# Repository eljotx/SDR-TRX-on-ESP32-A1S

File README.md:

# SDR-TRX-on-ESP32-A1S -> JACK
This repository describes an SDR transceiver based on the ESP32 A1S processor, using an ILI9341 color touchscreen display, and a Si5351 oscillator. The program was written on the Arduino platform and is still in development, but the most important features have already been implemented and tested.
The most important part of the software is Arduino Audio Tools, authored by Phil Schatzmann: https://github.com/pschatzmann/arduino-audio-tools

# General Idea

The transceiver was built using a phase-based SSB signal generation method. Due to the breadth of the topic and the abundance of descriptions available online, this method will not be described here. However, I encourage you to study this topic theoretically, which will help you understand the presented solution.

Crucial to the solution is the use of **Tayloe mixer on FST3253, A/D conversion, Hilbert transforms, digital filters, and D/A conversion** in the audio paths of the receiver and transmitter.

## Local oscilator 

The Si5351 acts as a local oscillator, clocking the transmitter and receiver mixers at a frequency that ensures proper detection or modulation. In this case, the clock signals have a frequency twice that of the useful signal, with an additional 90-degree shift between them, achieved using an additional shaping circuit based on integrated circuits 7474 and 7486. It is possible to generate the mixer signals directly within the Si5351, but for operation above 3.5 MHz, the controller needs to be modified, but the biggest inconvenience is the need to reset the PLL synchronization loop. This synchronization generates delays that are perceived as strong clicks during receive mode.

## Tayloe Mixer

The FST3253 is a dual, quadruple, high-speed digital keyer that acts as a keyed mixer for both the transmitter and receiver. During reception, the mixer extracts the I and Q components from the received signal for further digital processing. During transmission, it modulates the RF signal with I and Q components, creating a lower or upper sideband signal.

## Processor ESP32 A1S

The core of the system is the ESP32 A1S processor, which is suitable for implementing the project because it contains built-in internal A/D and D/A converters and operates at a speed that allows for sufficiently fast sampling and the use of digital filters of desired complexity. Although the A/D and D/A converters have a resolution of 16 bits, this seems sufficient for a design that doesn't aspire to perfection, but rather addresses basic digital processing issues. Additionally, the processor has two cores, allowing for the separation of tasks that don't require immediate processing from those related to audio streaming. An additional advantage of the processor is the ability to use two I2c channels for communication with peripherals and a channel SPI for communication with the display. All of these features are discussed in more detail in the following descriptions.

# How receiver works
The antenna signal reaches a Tayloe mixer, where I and Q signals are generated. Both signals contain sideband information, which is used for digital data processing. To achieve this, the analog I and Q signals are digitized using 16-bit A/D converters. A Hilbert transform is then applied to one of the channels (shifting the signal's phase by 90 degrees). The signals are then digitally filtered using a BiQuad digital filter. Three filters are available: two low-pass filters at 3.6 kHz and 2.4 kHz, and a bandpass filter at 800 Hz for CW reception. Finally, the I and Q signals are converted back to analog using 16-bit D/A converters and summed, reducing the sideband of the received signal. The received sideband is selected in the Tayloe mixer by changing the phase of the heterodyne signals, reducing the load on the digital software.

The figure shows the signal waveform during reception in more detail. The antenna signal passes through an adjustable PIN diode attenuator and an ERA6 amplifier, and is then detected in the Taylor mixer. The I and Q signals extracted from the mixer, after summing, detection, and amplification, are used to adjust the gain using the PIN attenuator, and also, through AGC signal measurement, visualize the received signal strength. Simultaneously, the extracted I and Q signals undergo digital processing, as described earlier, and after conversion to analog and amplification, they can be received via headphones or a loudspeaker.

# How transceiver works

## SSB mode
In SSB mode, the transmitter initially digitizes the microphone signal using A/D converters. Subsequently, a Hilbert transform is performed on one of the signals, followed by a common LPF digital filtering with a 2.4 kHz bandwidth. This creates two digital I and Q signals, which are then converted to analog using D/A converters. The SSB signal is formed in a Tayloe mixer using two heterodyne signals that are 90 degrees out of phase. Similar to receiving, the sideband is selected by determining which heterodyne signal has a +90 degree offset relative to the other. This signal is then amplified and fed to the antenna. 

## CW mode
In CW mode, the Tayloe mixer is disabled (heterodyne stop), and an additional keyed heterodyne is activated at the device's operating frequency, with a sideband offset of approximately +800 Hz, depending on the sideband used.

In addition to the previously described CW and SSB signal generation process, the figure shows how common circuit elements are used. Specifically, the microphone signal is pre-amplified in the same amplifier used for reception, and after shaping the I and Q channels, it feeds the Tayloe mixer. The final output signal is generated at the Tayloe mixer output in SSB mode or directly from the Si5351 generator in CW mode.

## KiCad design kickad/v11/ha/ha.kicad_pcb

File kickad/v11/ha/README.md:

The system can be operated in a basic configuration without the AGC system and redundant components. The drawing shows which components do not need to be installed in such a case.
The red markings refer to the PIN diode attenuator. The purple markings refer to the input amplifier, which results in reduced receiver sensitivity. In both cases, the jumpers marked in blue must be installed.

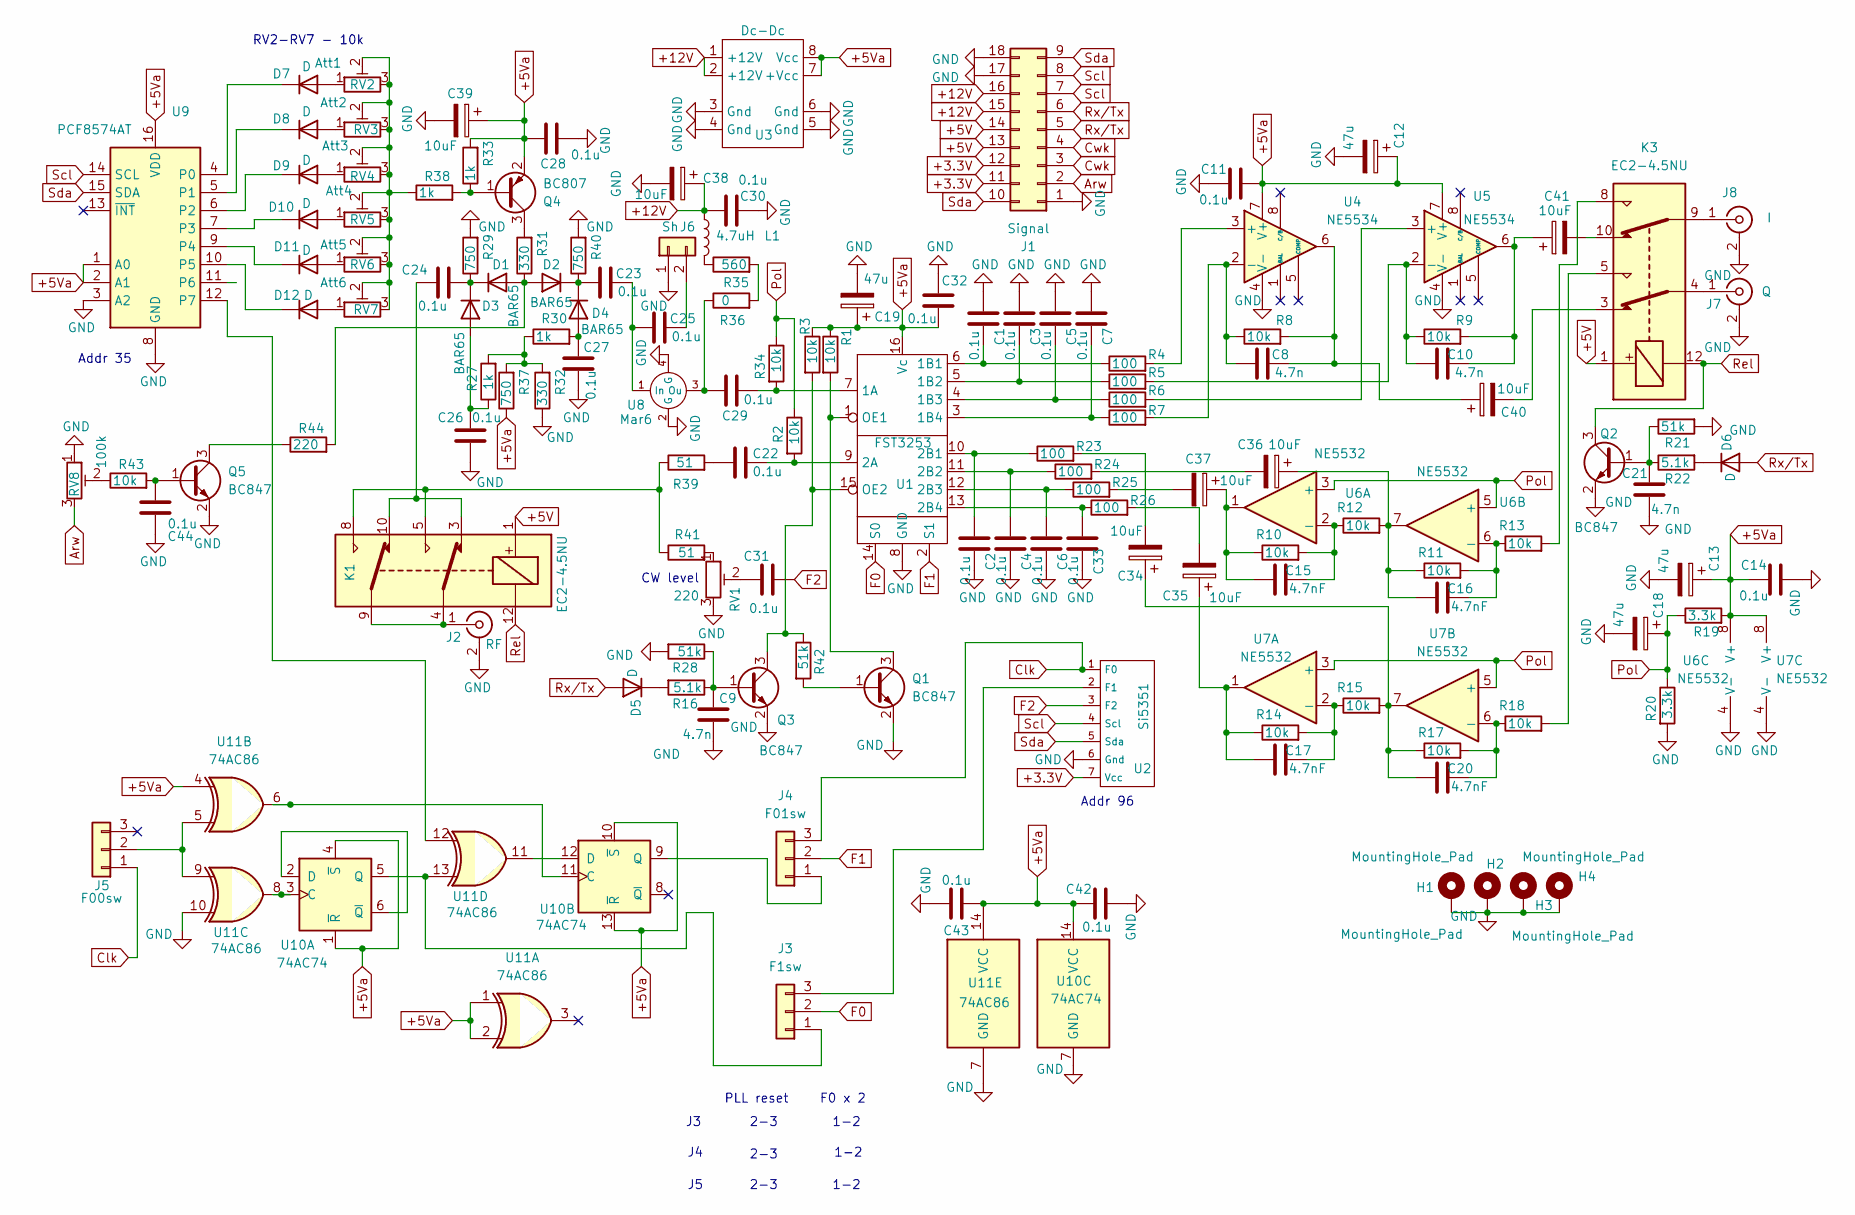
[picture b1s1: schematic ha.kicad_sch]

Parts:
C1, C2, C3, C4, C5, C6, C7, C11, C14, C22, C23, C24, C25, C26, C27, C28, C29, C30, C31, C32, C33, C42, C43, C44: 0.1u; C_0805_2012Metric
C8, C9, C10, C21: 4.7n; C_0805_2012Metric
C12, C13, C18, C19: 47u; CP_EIA-7343-31_Kemet-D
C15, C16, C17, C20: 4.7nF; C_0805_2012Metric
C34, C35, C36, C37, C38, C39, C40, C41: 10uF; C_1206_3216Metric
D1, D2, D3, D4: BAR65; C_0805_2012Metric
D5, D6, D7, D8, D9, D10, D11, D12: D; C_1206_3216Metric
H1, H2, H3, H4: MountingHole_Pad; MountingHole_3.2mm_M3_Pad_Via
J1: Signal; PinHeader_2x09_P2.54mm_Vertical
J2: RF; SMA_Amphenol_901-144_Vertical
J3: F1sw; PinHeader_1x03_P2.54mm_Vertical
J4: F01sw; PinHeader_1x03_P2.54mm_Vertical
J5: F00sw; PinHeader_1x03_P2.54mm_Vertical
J6: Sh; PinHeader_1x02_P2.54mm_Vertical
J7: Q; SMA_Amphenol_901-144_Vertical
J8: I; SMA_Amphenol_901-144_Vertical
K1, K3: EC2-4.5NU; Relay_DPDT_Kemet_EC2_NJ
L1: 4.7uH; L_Axial_L5.3mm_D2.2mm_P7.62mm_Horizontal_Vishay_IM-1
Q1, Q2, Q3, Q5: BC847; SOT-23
Q4: BC807; SOT-23
R1, R2, R3, R8, R9, R10, R11, R12, R13, R14, R15, R17, R18, R34, R43: 10k; R_0805_2012Metric
R4, R5, R6, R7, R23, R24, R25, R26: 100; R_0805_2012Metric
R16, R22: 5.1k; R_0805_2012Metric
R19, R20: 3.3k; R_0805_2012Metric
R21, R28, R42: 51k; R_0805_2012Metric
R27, R30, R33, R38: 1k; R_0805_2012Metric
R29, R37, R40: 750; R_0805_2012Metric
R31, R32: 330; R_0805_2012Metric
R35: 560; R_0805_2012Metric
R36: 0; R_0805_2012Metric
R39, R41: 51; R_0805_2012Metric
R44: 220; R_0805_2012Metric
RV1: 220; Potentiometer_ACP_CA6-H2,5_Horizontal
RV2: Att1; Potentiometer_ACP_CA6-H2,5_Horizontal
RV3: Att2; Potentiometer_ACP_CA6-H2,5_Horizontal
RV4: Att3; Potentiometer_ACP_CA6-H2,5_Horizontal
RV5: Att4; Potentiometer_ACP_CA6-H2,5_Horizontal
RV6: Att5; Potentiometer_ACP_CA6-H2,5_Horizontal
RV7: Att6; Potentiometer_ACP_CA6-H2,5_Horizontal
RV8: 100k; Potentiometer_ACP_CA6-H2,5_Horizontal
U1: FST3253; SOIC-16W_5.3x10.2mm_P1.27mm
U2: Si5351
U3: Dc-Dc; dc-dc
U4, U5: NE5534; SO-8_3.9x4.9mm_P1.27mm
U6, U7: NE5532; SO-8_3.9x4.9mm_P1.27mm
U8: Mar6; Era
U9: PCF8574AT; SOIC-16W_7.5x10.3mm_P1.27mm
U10: 74AC74; SO-14_5.3x10.2mm_P1.27mm
U11: 74AC86; SO-14_5.3x10.2mm_P1.27mm

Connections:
+3.3V: J1.11, J1.12, U2.7 (Vcc)
+5V: J1.13, J1.14, K1.1, K3.1
+5Va: C11.1, C12.1, C13.1, C14.2, C19.1, C28.1, C32.1, C39.1, C42.2, C43.2, Q4.2 (E), R1.1, R3.1, R19.2, R33.2, R37.1, U1.16 (Vc), U3.7 (+Vcc), U3.8 (Vcc), U4.7 (V+), U5.7 (V+), U6.8 (V+), U7.8 (V+), U9.1 (A0), U9.2 (A1), U9.16 (VDD), U10.1 (~R), U10.4 (~S), U10.10 (~S), U10.13 (~R), U10.14 (VCC), U11.1, U11.2, U11.4, U11.14 (VCC)
+12V: C30.2, C38.1, J1.15, J1.16, L1.1, U3.1 (+12V), U3.2 (+12V)
Arw: J1.2, RV8.3
Clk: J4.3, J5.1, U2.1 (F0)
Cwk: J1.3, J1.4
F0: J3.2, U1.14 (S0)
F1: J4.2, U1.2 (S1)
F2: C31.1, U2.3 (F2)
GND: C1.2, C2.1, C3.2, C4.1, C5.2, C6.1, C7.2, C9.1, C11.2, C12.2, C13.2, C14.1, C18.2, C19.2, C21.1, C26.2, C27.2, C28.2, C30.1, C32.2, C33.1, C38.2, C39.2, C42.1, C43.1, C44.1, H1.1, H2.1, H3.1, H4.1, J1.1, J1.17, J1.18, J2.2 (Ext), J6.1, J7.2 (Ext), J8.2 (Ext), Q1.2 (E), Q2.2 (E), Q3.2 (E), Q5.2 (E), R20.2, R21.2, R28.2, R29.2, R32.1, R40.2, RV1.3, RV8.1, U1.8 (GND), U2.6 (Gnd), U3.3 (Gnd), U3.4 (Gnd), U3.5 (Gnd), U3.6 (Gnd), U4.4 (V-), U5.4 (V-), U6.4 (V-), U7.4 (V-), U8.2 (G), U8.4 (G), U9.3 (A2), U9.8 (GND), U10.7 (GND), U11.7 (GND), U11.10
unnamed: C10.1, C41.1, R9.2, U5.6
unnamed: C15.2, C37.1, R10.1, U6.1
unnamed: C16.2, C36.1, R11.1, R12.2, U6.7
unnamed: C17.2, C35.1, R14.1, U7.1
unnamed: C20.2, C34.1, R15.2, R17.1, U7.7
unnamed: C22.2, R39.2
unnamed: C24.2, K1.3, K1.10
unnamed: C31.2, RV1.2
unnamed: C34.2, R23.2
unnamed: C35.2, R26.2
unnamed: C36.2, R24.2
unnamed: C37.2, R25.2
unnamed: C8.1, C40.1, R8.2, U4.6
unnamed: C40.2, K3.3
unnamed: C41.2, K3.10
unnamed: D1.2 (A), D2.2 (A), R31.1, R44.2
unnamed: C24.1, D1.1 (K), D3.1 (K), R29.1
unnamed: C23.2, D2.1 (K), D4.1 (K), R40.1
unnamed: C26.1, D3.2 (A), R27.1
unnamed: C27.1, D4.2 (A), R30.2
unnamed: D5.1 (K), R16.2
unnamed: D6.1 (K), R22.2
unnamed: D7.2 (A), RV2.1
unnamed: D7.1 (K), U9.4 (P0)
unnamed: D8.2 (A), RV3.1
unnamed: D8.1 (K), U9.5 (P1)
unnamed: D9.2 (A), RV4.1
unnamed: D9.1 (K), U9.6 (P2)
unnamed: D10.2 (A), RV5.1
unnamed: D10.1 (K), U9.7 (P3)
unnamed: D11.2 (A), RV6.1
unnamed: D11.1 (K), U9.9 (P4)
unnamed: D12.2 (A), RV7.1
unnamed: D12.1 (K), U9.10 (P5)
unnamed: J2.1 (In), K1.4, K1.9
unnamed: J3.1, U10.5 (Q), U11.13
unnamed: J3.3, U2.2 (F1)
unnamed: J4.1, U10.9 (Q)
unnamed: J5.2, U11.5, U11.9
unnamed: C25.1, J6.2
unnamed: J7.1 (In), K3.4
unnamed: J8.1 (In), K3.9
unnamed: K1.5, K1.8, R39.1, R41.1
unnamed: K3.5, R18.2
unnamed: K3.8, R13.2
unnamed: L1.2, R35.1
unnamed: Q1.1 (B), R42.2
unnamed: Q1.3 (C), R1.2, U1.1 (OE1)
unnamed: C21.2, Q2.1 (B), R21.1, R22.1
unnamed: C9.2, Q3.1 (B), R16.1, R28.1
unnamed: Q3.3 (C), R3.2, R42.1, U1.15 (OE2)
unnamed: Q4.1 (B), R33.1, R38.2
unnamed: Q4.3 (C), R31.2
unnamed: C44.2, Q5.1 (B), R43.2
unnamed: Q5.3 (C), R44.1
unnamed: R27.2, R30.1, R32.2, R37.2
unnamed: R35.2, R36.2
unnamed: R38.1, RV2.2, RV2.3, RV3.2, RV3.3, RV4.2, RV4.3, RV5.2, RV5.3, RV6.2, RV6.3, RV7.2, RV7.3
unnamed: R41.2, RV1.1
unnamed: R43.1, RV8.2
unnamed: C29.1, R34.2, U1.7 (1A)
unnamed: C1.1, R4.1, U1.6 (1B1)
unnamed: C3.1, R5.1, U1.5 (1B2)
unnamed: C5.1, R6.1, U1.4 (1B3)
unnamed: C7.1, R7.1, U1.3 (1B4)
unnamed: C22.1, R2.2, U1.9 (2A)
unnamed: C2.2, R23.1, U1.10 (2B1)
unnamed: C4.2, R24.1, U1.11 (2B2)
unnamed: C6.2, R25.1, U1.12 (2B3)
unnamed: C33.2, R26.1, U1.13 (2B4)
unnamed: R4.2, U4.3 (+)
unnamed: C8.2, R7.2, R8.1, U4.2 (-)
unnamed: R6.2, U5.3 (+)
unnamed: C10.2, R5.2, R9.1, U5.2 (-)
unnamed: C15.1, R10.2, R12.1, U6.2 (-)
unnamed: C16.1, R11.2, R13.1, U6.6 (-)
unnamed: C17.1, R14.2, R15.1, U7.2 (-)
unnamed: C20.1, R17.2, R18.1, U7.6 (-)
unnamed: C23.1, C25.2, U8.1 (In)
unnamed: C29.2, R36.1, U8.3 (Ou)
unnamed: U9.12 (P7), U11.12
unnamed: U10.3 (C), U11.8
unnamed: U10.2 (D), U10.6 (~Q)
unnamed: U10.11 (C), U11.6
unnamed: U10.12 (D), U11.11
Pol: C18.1, R2.1, R19.1, R20.1, R34.1, U6.3 (+), U6.5 (+), U7.3 (+), U7.5 (+)
Rel: K1.12, K3.12, Q2.3 (C)
Rx/Tx: D5.2 (A), D6.2 (A), J1.5, J1.6
Scl: J1.7, J1.8, U2.4 (Scl), U9.14 (SCL)
Sda: J1.9, J1.10, U2.5 (Sda), U9.15 (SDA)

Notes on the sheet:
2-3
1-2
Addr 96
Addr 35
F0 x 2
PLL reset
RV2-RV7 - 10k
CW level

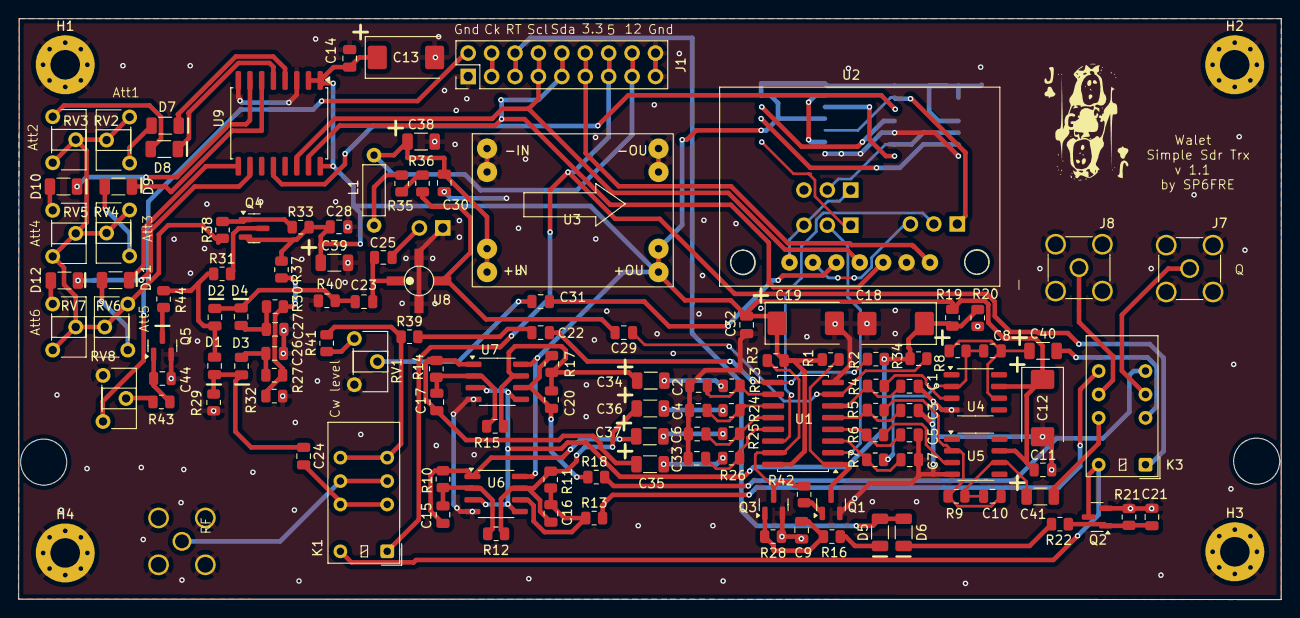
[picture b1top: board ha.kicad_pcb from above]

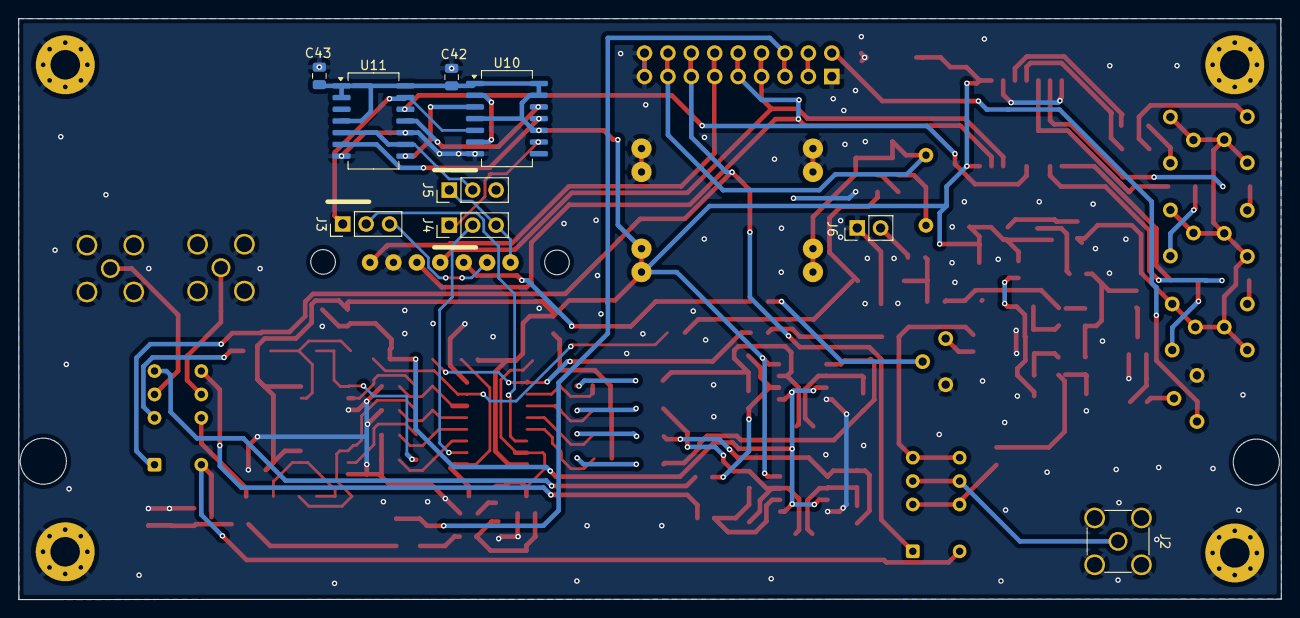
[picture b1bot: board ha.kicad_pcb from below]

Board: 2 copper layers, 137.0 x 63.0 mm, 139 parts (9 on the bottom side), 101 nets.

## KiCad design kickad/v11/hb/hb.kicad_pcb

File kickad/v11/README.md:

Kickad files was created with KicCad version 8.09-1

Software version 1_1 require using resistance divider (values) as showed on picture.

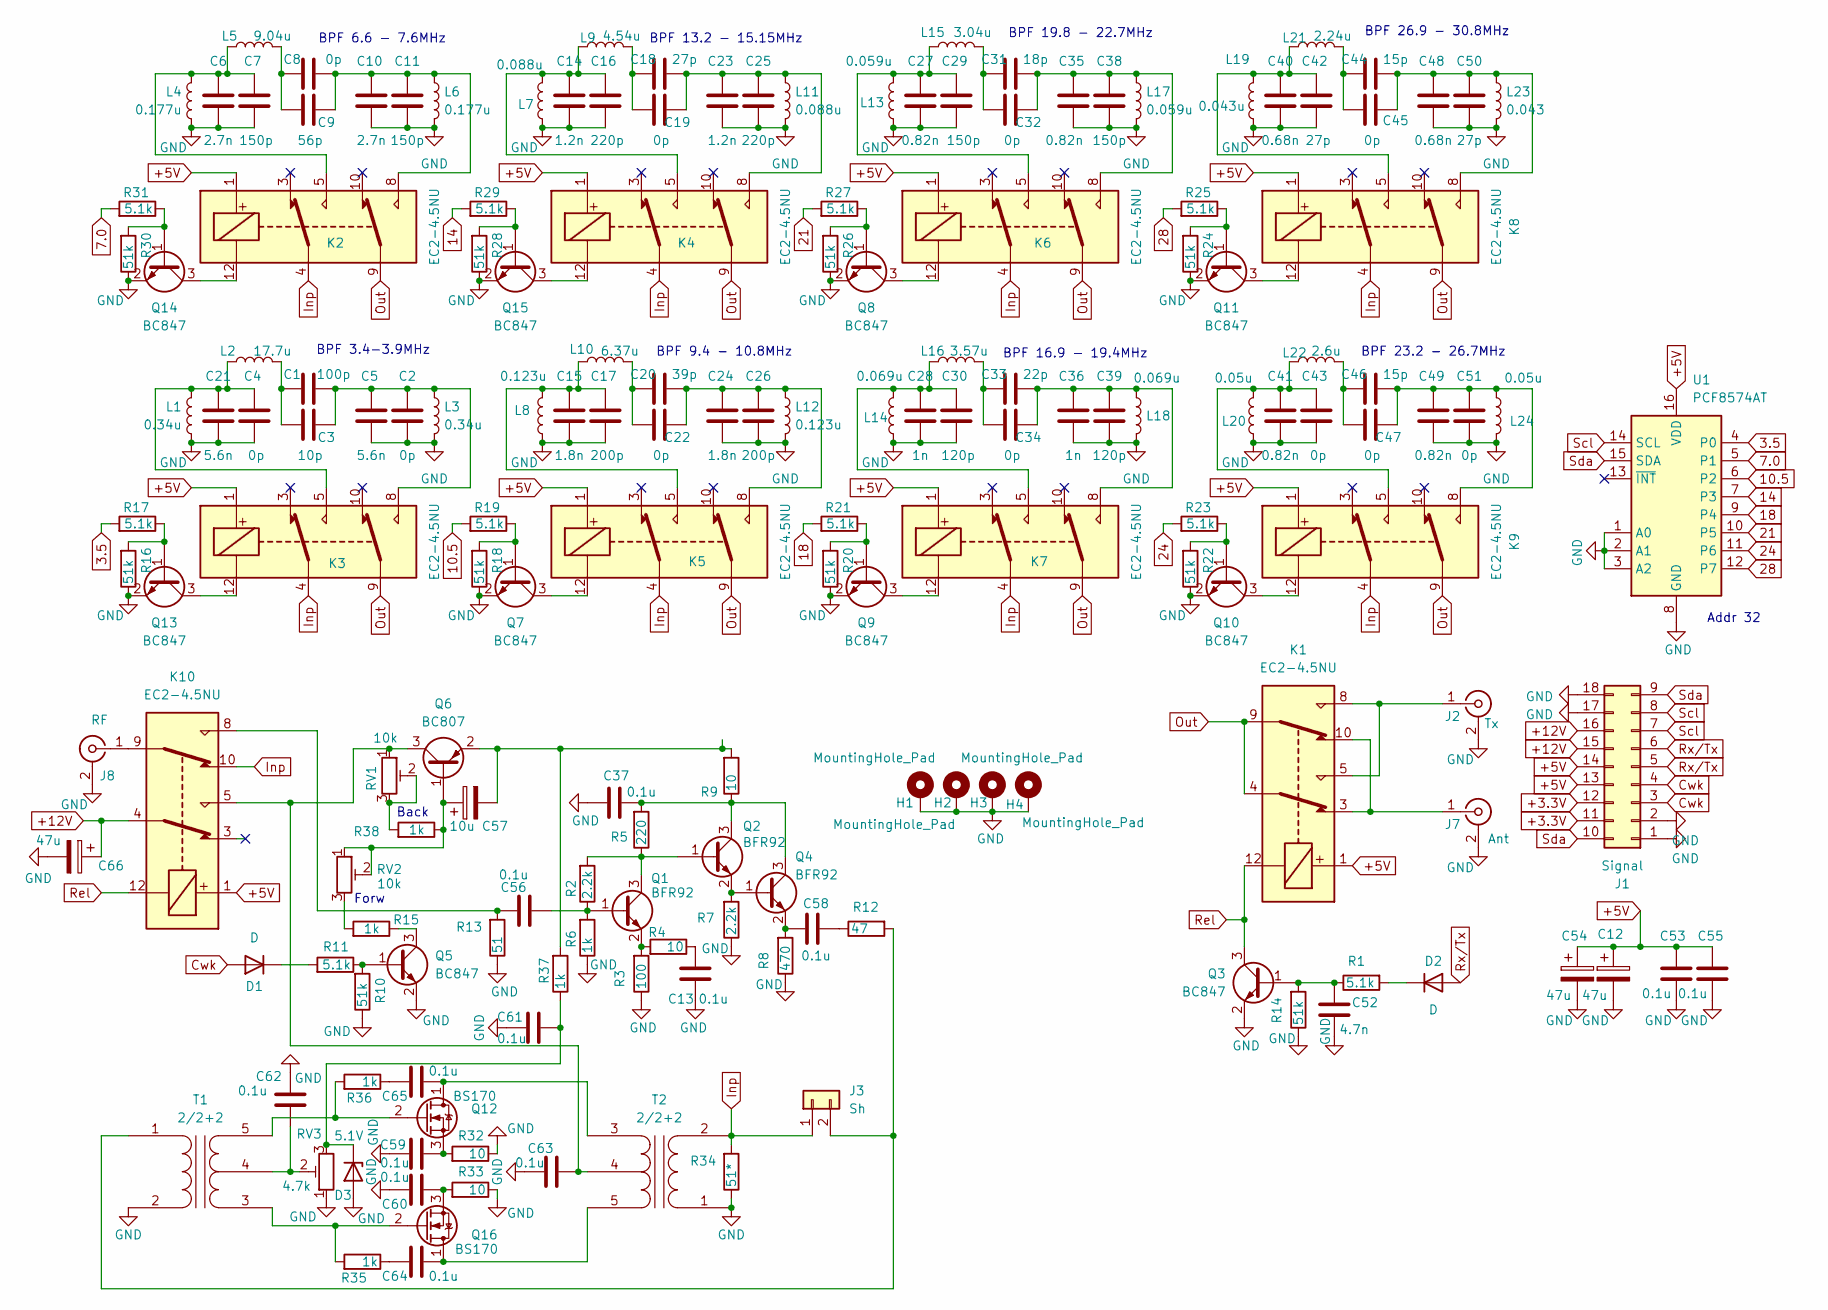
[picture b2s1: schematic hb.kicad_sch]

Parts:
C1: 10p; C_0805_2012Metric
C2, C4, C9, C18, C20, C31, C33, C43, C44, C46, C51: 0p; C_0805_2012Metric
C3: 100p; C_0805_2012Metric
C5, C21: 5.6n; C_0805_2012Metric
C6, C10: 2.7n; C_0805_2012Metric
C7, C11, C29, C38: 150p; C_0805_2012Metric
C8: 56p; C_0805_2012Metric
C12, C54, C66: 47u; CP_EIA-7343-31_Kemet-D
C13, C37, C53, C55, C56, C58, C59, C60, C61, C62, C63, C64, C65: 0.1u; C_0805_2012Metric
C14, C23: 1.2n; C_0805_2012Metric
C15, C24: 1.8n; C_0805_2012Metric
C16, C25: 220p; C_0805_2012Metric
C17, C26: 200p; C_0805_2012Metric
C19, C42, C50: 27p; C_0805_2012Metric
C22: 39p; C_0805_2012Metric
C27, C35, C41, C49: 0.82n; C_0805_2012Metric
C28, C36: 1n; C_0805_2012Metric
C30, C39: 120p; C_0805_2012Metric
C32: 18p; C_0805_2012Metric
C34: 22p; C_0805_2012Metric
C40, C48: 0.68n; C_0805_2012Metric
C45, C47: 15p; C_0805_2012Metric
C52: 4.7n; C_0805_2012Metric
C57: 10u; C_1206_3216Metric
D1, D2: D; C_1206_3216Metric
D3: 5.1V; C_1206_3216Metric
H1, H2, H3, H4: MountingHole_Pad; MountingHole_3.2mm_M3_Pad_Via
J1: Signal; PinHeader_2x09_P2.54mm_Vertical
J2: Tx; SMA_Amphenol_901-144_Vertical
J3: Sh; PinHeader_1x02_P2.54mm_Vertical
J7: Ant; SMA_Amphenol_901-144_Vertical
J8: RF; SMA_Amphenol_901-144_Vertical
K1, K2, K3, K4, K5, K6, K7, K8, K9, K10: EC2-4.5NU; Relay_DPDT_Kemet_EC2_NJ
L1, L3: 0.34u; l_01
L2: 17.7u; l_01
L4, L6: 0.177u; l_01
L5: 9.04u; l_01
L7, L11: 0.088u; l_01
L8, L12: 0.123u; l_01
L9: 4.54u; l_01
L10: 6.37u; l_01
L13, L17: 0.059u; l_01
L14, L18: 0.069u; l_01
L15: 3.04u; l_01
L16: 3.57u; l_01
L19: 0.043u; l_01
L20, L24: 0.05u; l_01
L21: 2.24u; l_01
L22: 2.6u; l_01
L23: 0.043; l_01
Q1, Q2, Q4: BFR92; SOT-23
Q3, Q5, Q7, Q8, Q9, Q10, Q11, Q13, Q14, Q15: BC847; SOT-23
Q6: BC807; SOT-23
Q12, Q16: BS170; TO-92_Inline
R1, R11, R17, R19, R21, R23, R25, R27, R29, R31: 5.1k; R_0805_2012Metric
R2, R7: 2.2k; R_0805_2012Metric
R3: 100; R_0805_2012Metric
R4, R9, R32, R33: 10; R_0805_2012Metric
R5: 220; R_0805_2012Metric
R6, R15, R35, R36, R37, R38: 1k; R_0805_2012Metric
R8: 470; R_0805_2012Metric
R10, R14, R16, R18, R20, R22, R24, R26, R28, R30: 51k; R_0805_2012Metric
R12: 47; R_0805_2012Metric
R13: 51; R_0805_2012Metric
R34: 51*; R_Axial_DIN0207_L6.3mm_D2.5mm_P10.16mm_Horizontal
RV1, RV2: 10k; Potentiometer_ACP_CA6-H2,5_Horizontal
RV3: 4.7k; Potentiometer_ACP_CA6-H2,5_Horizontal
T1, T2: 2/2+2; tr_05_v
U1: PCF8574AT; SOIC-16W_7.5x10.3mm_P1.27mm

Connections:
3.5: R17.2, U1.4 (P0)
7.0: R31.2, U1.5 (P1)
10.5: R19.2, U1.6 (P2)
14: R29.2, U1.7 (P3)
18: R21.2, U1.9 (P4)
21: R27.2, U1.10 (P5)
24: R23.2, U1.11 (P6)
28: R25.2, U1.12 (P7)
+3.3V: J1.11, J1.12
+5V: C12.1, C53.2, C54.1, C55.2, J1.13, J1.14, K1.1, K2.1, K3.1, K4.1, K5.1, K6.1, K7.1, K8.1, K9.1, K10.1, U1.16 (VDD)
+12V: C66.1, J1.15, J1.16, K10.4
Cwk: D1.2 (A), J1.3, J1.4
GND: C2.1, C4.1, C5.1, C6.1, C7.1, C10.1, C11.1, C12.2, C13.1, C14.1, C15.1, C16.1, C17.1, C21.1, C23.1, C24.1, C25.1, C26.1, C27.1, C28.1, C29.1, C30.1, C35.1, C36.1, C37.2, C38.1, C39.1, C40.1, C41.1, C42.1, C43.1, C48.1, C49.1, C50.1, C51.1, C52.1, C53.1, C54.2, C55.1, C59.2, C60.2, C61.1, C62.1, C63.2, C66.2, D3.2 (A), H1.1, H2.1, H3.1, H4.1, J1.1, J1.2, J1.17, J1.18, J2.2 (Ext), J7.2 (Ext), J8.2 (Ext), L1.2, L3.2, L4.2, L6.2, L7.2, L8.2, L11.2, L12.2, L13.2, L14.2, L17.2, L18.2, L19.2, L20.2, L23.2, L24.2, Q3.2 (E), Q5.2 (E), Q7.2 (E), Q8.2 (E), Q9.2 (E), Q10.2 (E), Q11.2 (E), Q13.2 (E), Q14.2 (E), Q15.2 (E), R3.1, R6.1, R7.1, R8.1, R10.1, R13.1, R14.1, R16.1, R18.1, R20.1, R22.1, R24.1, R26.1, R28.1, R30.1, R32.1, R33.1, R34.1, RV3.1, T1.2 (AB), T2.1 (AA), U1.1 (A0), U1.2 (A1), U1.3 (A2), U1.8 (GND)
Inp: J3.1, K2.4, K3.4, K4.4, K5.4, K6.4, K7.4, K8.4, K9.4, K10.10, R34.2, T2.2 (AB)
unnamed: C1.1, C2.2, C3.1, C5.2, K3.8, L3.1
unnamed: C1.2, C3.2, L2.2
unnamed: C6.2, C7.2, K2.5, L4.1, L5.1
unnamed: C8.2, C9.2, L5.2
unnamed: C8.1, C9.1, C10.2, C11.2, K2.8, L6.1
unnamed: C13.2, R4.1
unnamed: C14.2, C16.2, K4.5, L7.1, L9.1
unnamed: C15.2, C17.2, K5.5, L8.1, L10.1
unnamed: C18.1, C19.1, C23.2, C25.2, K4.8, L11.1
unnamed: C18.2, C19.2, L9.2
unnamed: C20.1, C22.1, C24.2, C26.2, K5.8, L12.1
unnamed: C20.2, C22.2, L10.2
unnamed: C4.2, C21.2, K3.5, L1.1, L2.1
unnamed: C27.2, C29.2, K6.5, L13.1, L15.1
unnamed: C28.2, C30.2, K7.5, L14.1, L16.1
unnamed: C31.1, C32.1, C35.2, C38.2, K6.8, L17.1
unnamed: C31.2, C32.2, L15.2
unnamed: C33.1, C34.1, C36.2, C39.2, K7.8, L18.1
unnamed: C33.2, C34.2, L16.2
unnamed: C40.2, C42.2, K8.5, L19.1, L21.1
unnamed: C41.2, C43.2, K9.5, L20.1, L22.1
unnamed: C44.1, C45.1, C48.2, C50.2, K8.8, L23.1
unnamed: C44.2, C45.2, L21.2
unnamed: C46.1, C47.1, C49.2, C51.2, K9.8, L24.1
unnamed: C46.2, C47.2, L22.2
unnamed: C56.2, K10.8, R13.2
unnamed: C58.1, R12.1
unnamed: C64.2, R35.1
unnamed: C65.2, R36.1
unnamed: D1.1 (K), R11.2
unnamed: D2.1 (K), R1.2
unnamed: C61.2, D3.1 (K), R37.1, RV3.3
unnamed: J2.1 (In), K1.5, K1.8
unnamed: J3.2, R12.2, T1.1 (AA)
unnamed: J7.1 (In), K1.3, K1.10
unnamed: J8.1 (In), K10.9
unnamed: C56.1, Q1.1 (B), R2.1, R6.2
unnamed: Q1.3 (C), Q2.1 (B), R2.2, R5.1
unnamed: Q1.2 (E), R3.2, R4.2
unnamed: C37.1, Q2.3 (C), Q4.3 (C), R5.2, R9.1
unnamed: Q2.2 (E), Q4.1 (B), R7.2
unnamed: C52.2, Q3.1 (B), R1.1, R14.2
unnamed: C58.2, Q4.2 (E), R8.2
unnamed: Q5.1 (B), R10.2, R11.1
unnamed: Q5.3 (C), R15.1
unnamed: C57.1, Q6.1 (B), R38.1, RV2.1, RV2.2
unnamed: C63.1, K10.5, Q6.3 (C), RV1.1, T2.4 (SC)
unnamed: C57.2, Q6.2 (E), R9.2, R37.2
unnamed: Q7.1 (B), R18.2, R19.1
unnamed: K5.12, Q7.3 (C)
unnamed: Q8.1 (B), R26.2, R27.1
unnamed: K6.12, Q8.3 (C)
unnamed: Q9.1 (B), R20.2, R21.1
unnamed: K7.12, Q9.3 (C)
unnamed: Q10.1 (B), R22.2, R23.1
unnamed: K9.12, Q10.3 (C)
unnamed: Q11.1 (B), R24.2, R25.1
unnamed: K8.12, Q11.3 (C)
unnamed: C65.1, Q12.1 (D), T2.3 (SA)
unnamed: Q12.2 (G), R36.2, T1.5 (SB)
unnamed: C59.1, Q12.3 (S), R32.2
unnamed: Q13.1 (B), R16.2, R17.1
unnamed: K3.12, Q13.3 (C)
unnamed: Q14.1 (B), R30.2, R31.1
unnamed: K2.12, Q14.3 (C)
unnamed: Q15.1 (B), R28.2, R29.1
unnamed: K4.12, Q15.3 (C)
unnamed: C64.1, Q16.1 (D), T2.5 (SB)
unnamed: Q16.2 (G), R35.2, T1.3 (SA)
unnamed: C60.1, Q16.3 (S), R33.2
unnamed: R15.2, RV2.3
unnamed: R38.2, RV1.2, RV1.3
unnamed: C62.2, RV3.2, T1.4 (SC)
Out: K1.4, K1.9, K2.9, K3.9, K4.9, K5.9, K6.9, K7.9, K8.9, K9.9
Rel: K1.12, K10.12, Q3.3 (C)
Rx/Tx: D2.2 (A), J1.5, J1.6
Scl: J1.7, J1.8, U1.14 (SCL)
Sda: J1.9, J1.10, U1.15 (SDA)

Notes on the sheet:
Forw
BPF 9.4 - 10.8MHz
BPF 16.9 - 19.4MHz
BPF 19.8 - 22.7MHz
Addr 32
BPF 23.2 - 26.7MHz
BPF 26.9 - 30.8MHz
BPF 6.6 - 7.6MHz
BPF 13.2 - 15.15MHz
Back
BPF 3.4-3.9MHz

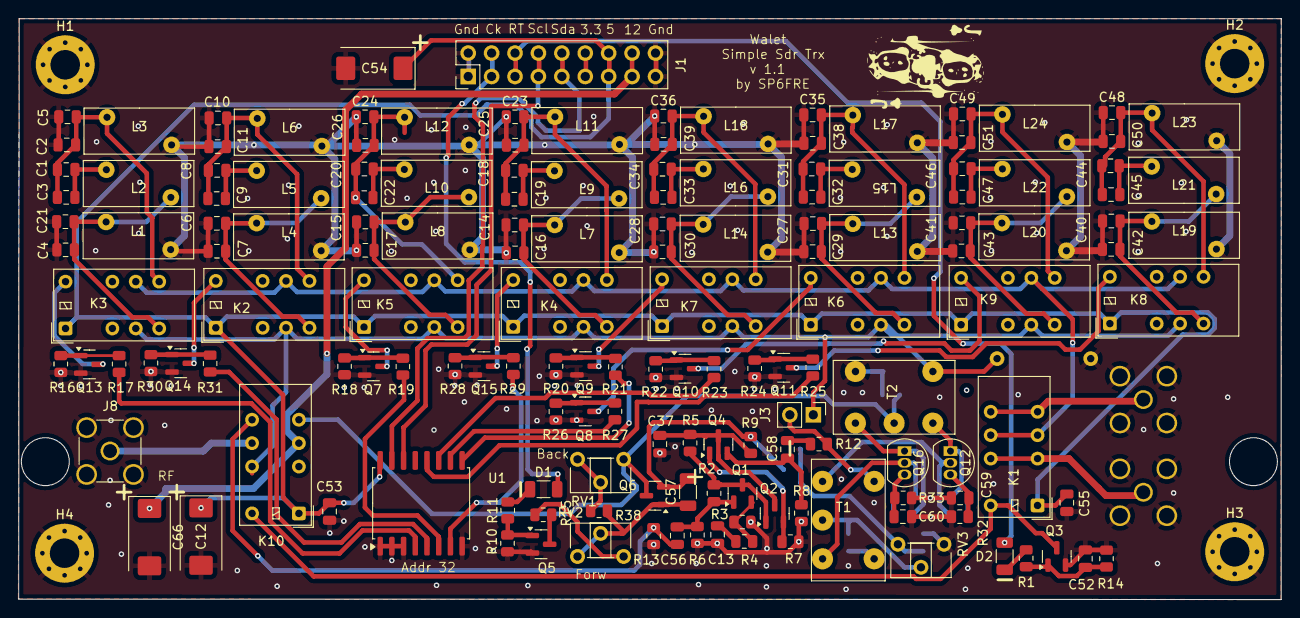
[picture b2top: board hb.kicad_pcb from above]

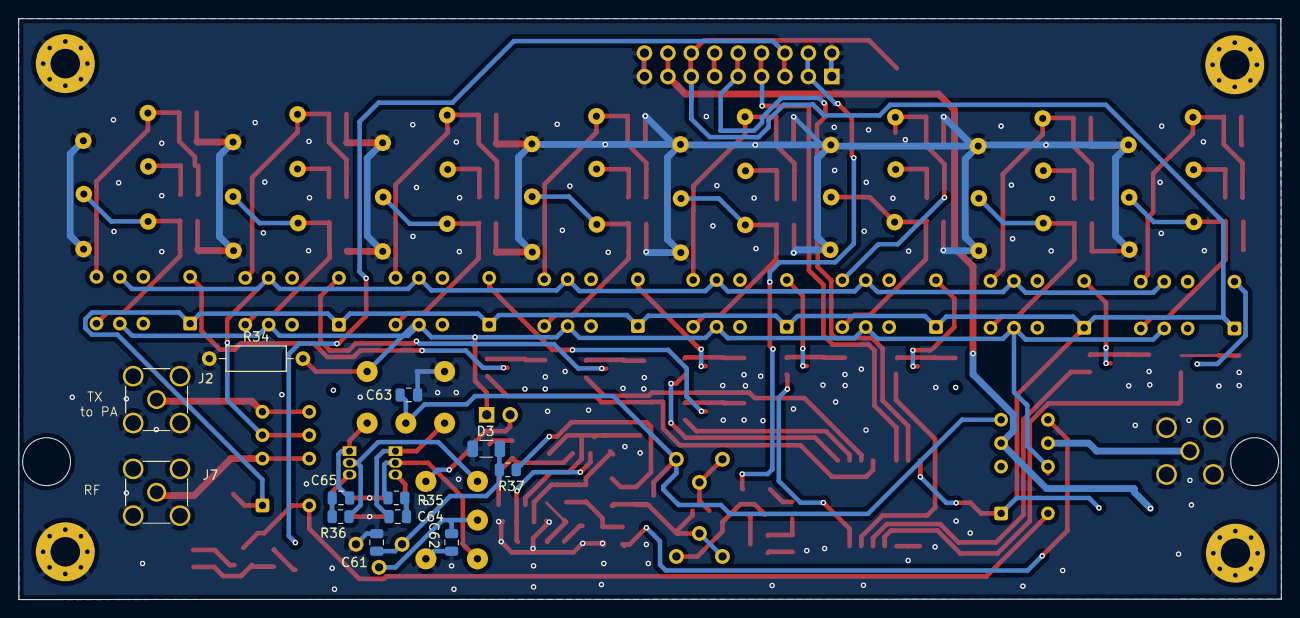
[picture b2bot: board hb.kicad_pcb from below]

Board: 2 copper layers, 137.0 x 63.0 mm, 172 parts (12 on the bottom side), 92 nets.
